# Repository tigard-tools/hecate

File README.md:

# Hecate
Hecate: A Trivial UART tool

# Objectives
UART is pervasive. Nearly every piece of hardware can speak it. It can be a treasure trove of access when it's not properly secured, an entrypoint to explore even when it is secured, and often a spot to tap plaintext communications between devices.

Hecate is a CircuitPython framework designed to make it quick and easy to work with UART data streams, both interactively and standalone. Hecate makes it possible to implement a customized UART logger, payload dropper, implant-in-the-middle, and more with little or no code.

# Inspiration
* [Akheron-proxy](https://github.com/rapid7/akheron-proxy) is a python tool for inspecting and manipulating inter-chip UART communications
* [Serberus](https://github.com/google/serberus) is a USB-to-multiple-UART device intended to work with Akheron-proxy and other tools. It was presented at [Crowdsupply's Teardown conference](https://www.youtube.com/watch?v=c6WhOVPHBbU) 
* [Circuitpython-uart-passthrough](https://github.com/scogswell/circuitpython-uart-passthrough) is a bare bones UART passthrough that is the starting point of many customizations that Hecate hopes to make a little more trivial

In Greek mythology, Akheron is the river Charon ferries the dead across and Cerberus is the 3-headed guard dog that guards the underworld. In keeping with the theme, Hecate is a goddess of crossroads. It's typically pronounced "eh-kah-tee" but you're more than welcome to pronounce it like "Tecate".

# Essential Features
* **Passthrough Device:** When not doing anything else, Hecate should be able to sit in the middle of a UART line, passing through all traffic with minimal (sub-millisecond) delays
* **Tap or Tee** In addition to passing through data, Hecate should be able to mirror a copy of that data to an additional UART or to a USB-serial interface.
* **Standalone Logger:** Without any USB host involved, Hecate should be able to log all UART traffic that passes through it to a text file. The text file will be retrievable by plugging the device in over USB and copying it off like a flash drive.
* **Payload Dropper** Without any USB host involved, Hecate should be able to transmit over UART the contents of a text file stored in it's EEPROM.
* **Pattern Detector** Hecate should be able to have basic pattern matching so that when a device transmits a preconfigured UART sequence, it triggers an additional action.
* **Pattern Patcher** Hecate should also be able to match/patch basic sequences to 
* **Triggers** Hecate should be able to do any of these things, triggered or enabled by button presses, timestamps, or other stimuli
* **Alerts** Hecate should be able to fire alerts such as LED output or other UART actions
* **Extensible** Users should be able to implement custom Triggers or Alerts, like temperature sensors or buzzers or wireless actions.

# Installing and Using Hecate

## Flashing with `make` (recommended, esp. for many boards)

On Linux you can flash CircuitPython **and** Hecate in one step. Hold **BOOTSEL**
while plugging a Xiaomao in (it appears as the `RPI-RP2` drive), then:

```
make all         # flash CircuitPython, wait for reboot, copy Hecate
make forever     # hub mode: repeat for each board you plug in, until Ctrl-C
make hecate      # just (re)copy Hecate onto an already-CircuitPython board
make list        # show detected boards
```

`make` pulls the pinned tigard-tools CircuitPython `.uf2` on first use (cached
in `firmware/`, offline afterwards; drop your own at `firmware/firmware.uf2` to
override). `forever` skips the firmware step for boards that already run this
build, and handles a hub full of same-labelled drives by tracking each device
as it appears. Mounting uses `sudo` on boxes with no automounter (set `SUDO=`
if you're root). Target-board (keypad/authorizer) flashing is a TODO stub — see
the `Makefile`. Details: `make help`.

## Manual install

1. Install CircuitPython on your device:
   * If you're using Xiaomao, you can download [firmware.U2F](https://github.com/tigard-tools/circuitpython/releases/tag/second-try) and copy it to your board.
   * For any other CircuitPython board, [download the firmware from circuitpython.org](https://circuitpython.org/downloads) and follow the instructions to flash it. 
1. Copy everything from the CIRCUITPY directory to your device:
   * Either clone this repository or download a release and unzip the files
   * Connect your board. If CircuitPython is properly installed, a drive named CIRCUITPY should appear
   * Copy all the files over to the CircuitPython drive
   * The Drive should have a folder named lib and files named code.py and boot.py. It should not contain another folder named CIRCUITPY
1. **Recommended for workshops — the Web Console.** Instead of juggling a
   serial terminal and a text editor, you can drive the whole thing from a
   browser. In the `web/` directory run `python3 -m http.server`, open
   `http://localhost:8000/` in Chrome/Edge/Brave, and you get the live monitor,
   a file browser, and a `code.py` editor in one page — no `screen`/`nano`
   needed. See [`web/README.md`](web/README.md) for details.
1. To work interactively with your device the classic way, connect to the usb serial interface:
   * On Linux systems, this could be typing 'screen /dev/ttyACM0' on a terminal
   * If you're using mu or circuitpy.dev, you can access the console from those programs
   * Each line on the monitor is tagged with a `<timestamp> [<wire>]` header so you can tell which wire (or Hecate itself) produced it.
   * You can type commands at the monitor: `help` lists them, `status` reports what lit the red status LED, and `exit` tells you how to detach your terminal and quiets the port (Hecate keeps running). Set `monitor_headers=False` on `Hecate(...)` if you'd rather see raw bytes.
1. To edit the standalone code on your device, open the code.py file found on the USB storage that shows up when you plug it in

### Saving Files
If you're using Xiaomao or another RP2040-based device, the files on your device are stored in the SPI flash chip. Who can write to thos files is managed by some code in boot.py
* When you plug in over USB, you can read and write those files from your computer, but your code can only read them
* When it is self-powered, your code can read and write those files. USB, if it is later connected, can only read them.
* To change the access mode - meaning, you want your code to be able to write files while you're plugged in over USB - make sure boot.py is on your device, then hold down the BTN as you power it on.

# Recommended Hardware
[Xiaomao](https://github.com/tigard-tools/xiaomao) is an RP2040-based device that can run CircuitPython, has 2 hardware UARTs, lives under the Tigard-Tools umbrella, and should work well with Hecate. Otherwise, any device that can run CircuitPython and has a UART should work just as well with Hecate.

In order to use Hecate implant-style in a system, you'll need to find a way to get power from the target device. Your implant's power requirements may vary.

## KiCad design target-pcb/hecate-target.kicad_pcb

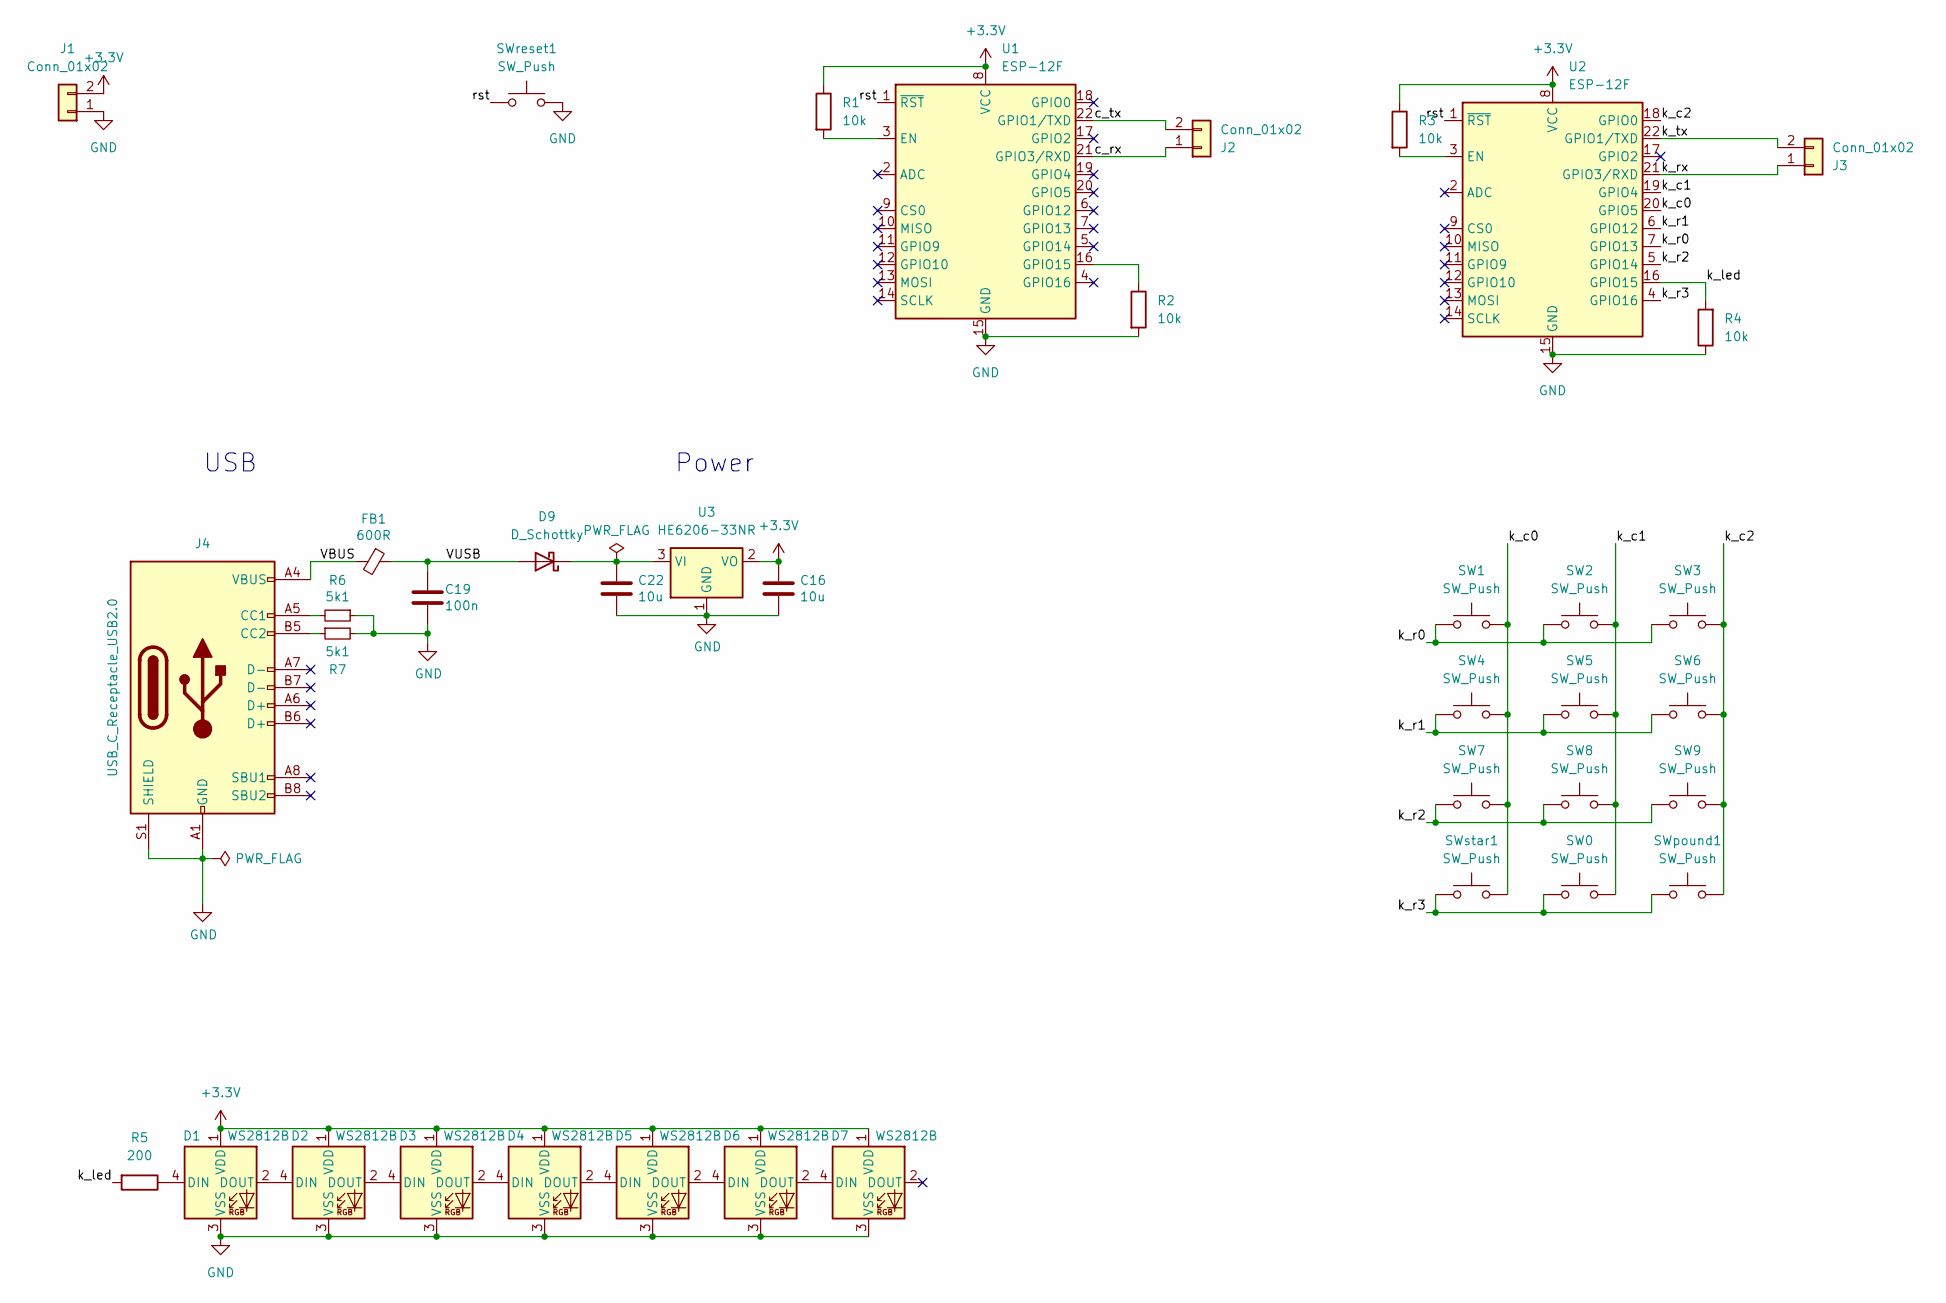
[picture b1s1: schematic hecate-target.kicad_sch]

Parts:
C16, C22: 10u; C_0402_1005Metric; LCSC C15525
C19: 100n; C_0402_1005Metric; LCSC C1525
D1, D2, D3, D4, D5, D6, D7: WS2812B; LED_WS2812B_PLCC4_5.0x5.0mm_P3.2mm; LCSC C2843785
D9: D_Schottky; D_SOD-523; LCSC C5310951
FB1: 600R; L_0603_1608Metric; LCSC C1002
J1, J2, J3: Conn_01x02; PinHeader_1x02_P2.54mm_Horizontal_SMD; LCSC C46061675
J4: USB_C_Receptacle_USB2.0; USB_C_Receptacle_HRO_TYPE-C-31-M-12; LCSC C2927038
R1, R2, R3, R4: 10k; R_0402_1005Metric; LCSC C25752
R5: 200; R_0402_1005Metric; LCSC C25087
R6, R7: 5k1; R_0402_1005Metric; LCSC C25905
SW0, SW1, SW2, SW3, SW4, SW5, SW6, SW7, SW8, SW9: SW_Push; SW_SPST_B3U-1000P; LCSC C2905193
SWpound1: SW_Push; SW_SPST_B3U-1000P; LCSC C2905193
SWreset1: SW_Push; SW_SPST_B3U-1000P; LCSC C2905193
SWstar1: SW_Push; SW_SPST_B3U-1000P; LCSC C2905193
U1, U2: ESP-12F; ESP-12E; LCSC C89297
U3: HE6206-33NR; SOT-23-3; LCSC C5199441

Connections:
+3.3V: C16.1, D1.1 (VDD), D2.1 (VDD), D3.1 (VDD), D4.1 (VDD), D5.1 (VDD), D6.1 (VDD), D7.1 (VDD), J1.2, R1.1, R3.1, U1.8 (VCC), U2.8 (VCC), U3.2 (VO)
/VBUS: FB1.2, J4.A4 (VBUS), J4.A9 (VBUS), J4.B4 (VBUS), J4.B9 (VBUS)
/VUSB: C19.1, D9.2 (A), FB1.1
/c_rx: J2.1, U1.21 (GPIO3/RXD)
/c_tx: J2.2, U1.22 (GPIO1/TXD)
/k_c0: SW1.2, SW4.2, SW7.2, SWstar1.2, U2.20 (GPIO5)
/k_c1: SW0.2, SW2.2, SW5.2, SW8.2, U2.19 (GPIO4)
/k_c2: SW3.2, SW6.2, SW9.2, SWpound1.2, U2.18 (GPIO0)
/k_led: R4.2, R5.2, U2.16 (GPIO15)
/k_r0: SW1.1, SW2.1, SW3.1, U2.7 (GPIO13)
/k_r1: SW4.1, SW5.1, SW6.1, U2.6 (GPIO12)
/k_r2: SW7.1, SW8.1, SW9.1, U2.5 (GPIO14)
/k_r3: SW0.1, SWpound1.1, SWstar1.1, U2.4 (GPIO16)
/k_rx: J3.1, U2.21 (GPIO3/RXD)
/k_tx: J3.2, U2.22 (GPIO1/TXD)
/rst: SWreset1.1, U1.1 (~RST), U2.1 (~RST)
GND: C16.2, C19.2, C22.2, D1.3 (VSS), D2.3 (VSS), D3.3 (VSS), D4.3 (VSS), D5.3 (VSS), D6.3 (VSS), D7.3 (VSS), J1.1, J4.A1 (GND), J4.A12 (GND), J4.B1 (GND), J4.B12 (GND), J4.S1 (SHIELD), R2.2, R4.1, R6.1, R7.2, SWreset1.2, U1.15 (GND), U2.15 (GND), U3.1 (GND)
unnamed: D1.4 (DIN), R5.1
unnamed: D1.2 (DOUT), D2.4 (DIN)
unnamed: D2.2 (DOUT), D3.4 (DIN)
unnamed: D3.2 (DOUT), D4.4 (DIN)
unnamed: D4.2 (DOUT), D5.4 (DIN)
unnamed: D5.2 (DOUT), D6.4 (DIN)
unnamed: D6.2 (DOUT), D7.4 (DIN)
unnamed: C22.1, D9.1 (K), U3.3 (VI)
unnamed: J4.A5 (CC1), R6.2
unnamed: J4.B5 (CC2), R7.1
unnamed: R1.2, U1.3 (EN)
unnamed: R2.1, U1.16 (GPIO15)
unnamed: R3.2, U2.3 (EN)

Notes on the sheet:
Power
USB

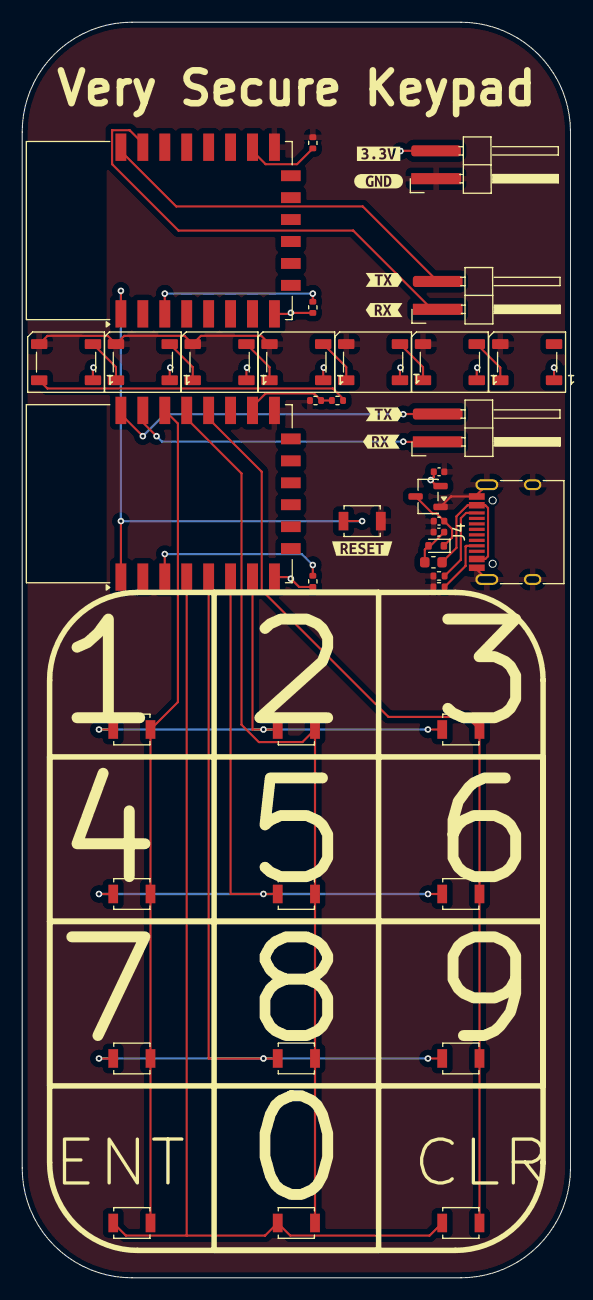
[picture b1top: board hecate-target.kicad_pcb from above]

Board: 2 copper layers, 50.0 x 114.5 mm, 46 parts (0 on the bottom side), 30 nets.

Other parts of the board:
kibuzzard-6A5751B8, kibuzzard-6A5751B8#2: G***; kibuzzard-6A5751B8
kibuzzard-6A5758F9: G***; kibuzzard-6A5758F9
kibuzzard-6A575194, kibuzzard-6A575194#2: G***; kibuzzard-6A575194
kibuzzard-6A575206: G***; kibuzzard-6A575206
kibuzzard-6A575238: G***; kibuzzard-6A575238

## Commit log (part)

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2026-05-01 adding inital pass at description, background, and overview.
2026-05-08 details about installing hecate
